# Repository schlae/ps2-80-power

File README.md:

# IBM PS/2 Model 80 Power Supply Schematics

There are multiple types of power supplies for these machines. This one is for the one marked 72X6665 / PEC 3978. This is the red switch 225W model.

## Notes

The design is an LLC resonant converter. It has a rather interesting auxiliary bias supply to power the PWM controller, so technically it is two supplies in one box.

* Inrush current into the main reservoir capacitors is limited by R117/118 and RT1/RT2. The capacitors are tied in series (to handle the 220V input case) with balancing resistors.
* The bias supply uses a preregulator that detects ~180V Vp-p and, partway through every AC cycle, cuts off a triac connected in series with a plain-old linear transformer isolated power supply. This ensures that the VCC bias supply has roughly the same voltage regardless of whether it is connected to 120V or 220V.
* The PWM controller is a SG3524 with external transistors that drive an isolation transformer in order to control the BJTs in the main power stage on the non-isolated side. The output voltage trim is set by R77, which samples both the +5V and +12V rail.
* An overcurrent comparator monitors the ripple current through the main power transformer and latches off the PWM controller if it exceeds a threshold. It also monitors the current *difference* between the two Schottky diodes in the 12V secondary side, presumably to detect Schottky diode failures.
* Every voltage (+12, -12V, +5V) is monitored for overvoltage and undervoltage. Overvoltages cause the supply to latch off. Undervoltage just deasserts the power good. Trimmer potentiometer R50 adjusts the voltage reference used by the comparators.
* The power LED is driven by the power good signal.
* The HDD LED is driven by a signal from the planar (motherboard).

## License
This work is licensed under Creative Commons Attribution-ShareAlike 4.0 International.
(C) 2024 Tube Time.

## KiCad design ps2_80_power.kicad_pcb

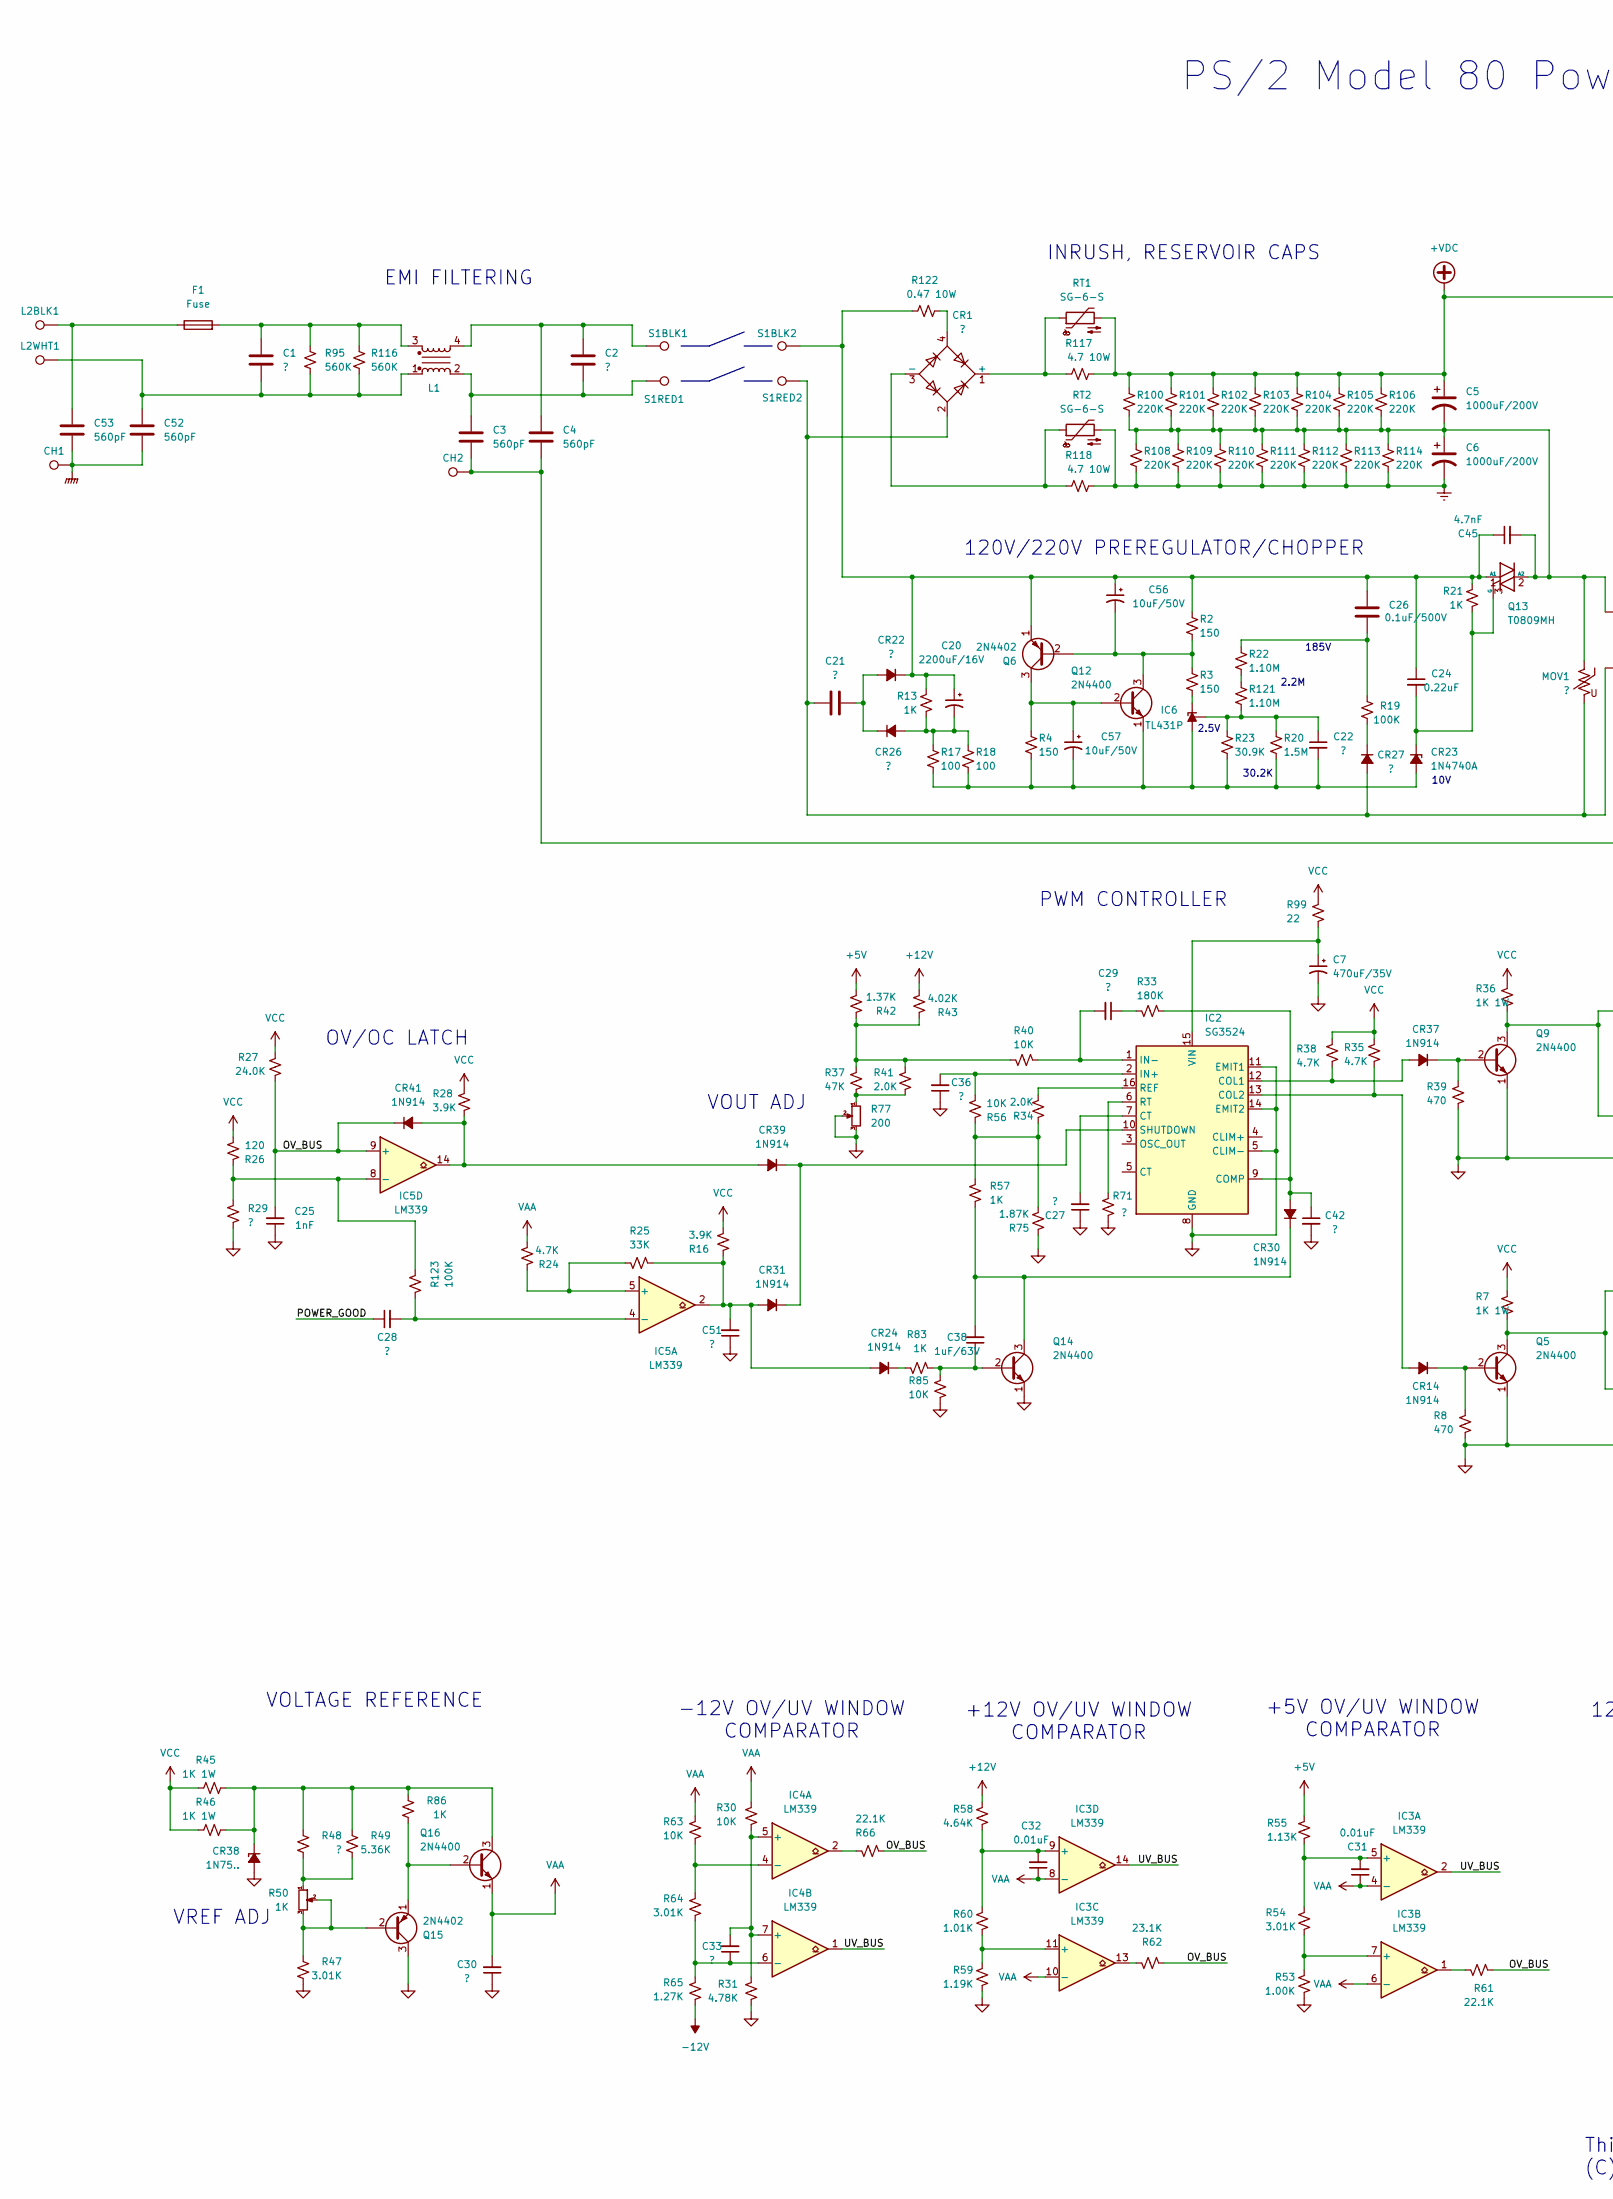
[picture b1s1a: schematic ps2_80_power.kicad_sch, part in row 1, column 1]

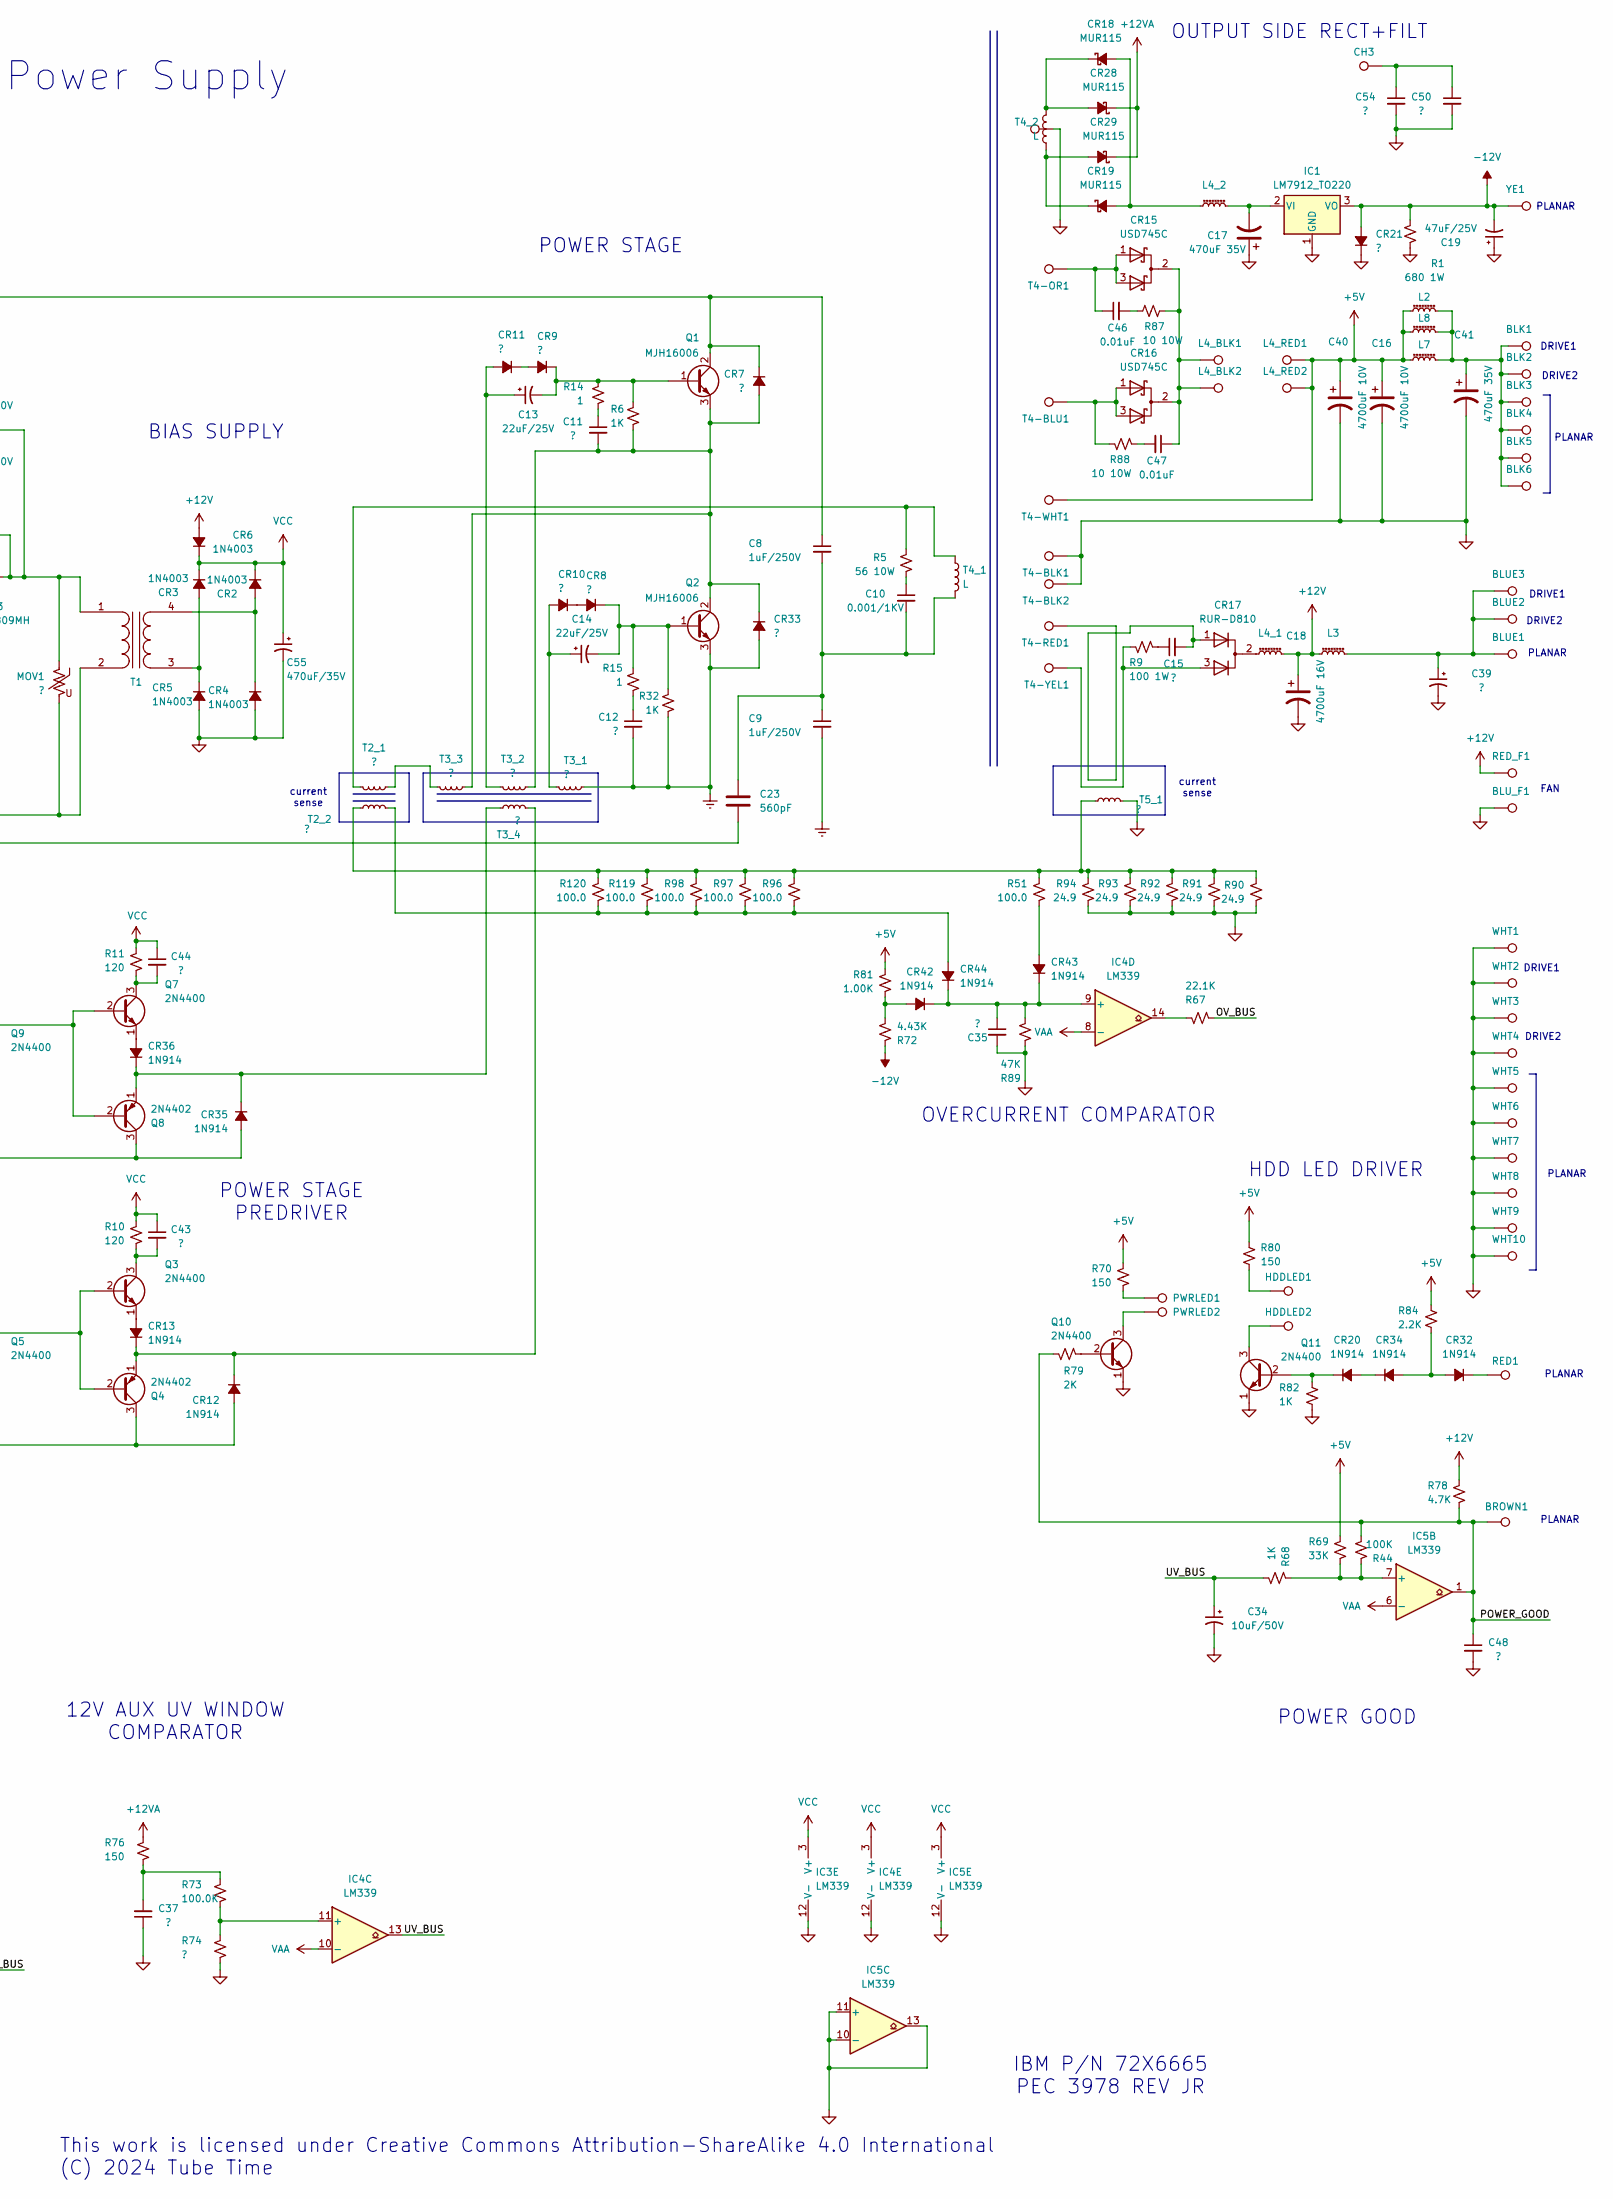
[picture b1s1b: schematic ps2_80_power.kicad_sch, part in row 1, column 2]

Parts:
BLK1, BLK2, BLK3, BLK4, BLK5, BLK6: TestPoint; SolderWire-1sqmm_1x01_D1.4mm_OD2.7mm
BLUE1, BLUE2, BLUE3: TestPoint; SolderWire-1sqmm_1x01_D1.4mm_OD2.7mm
BLU_F1: TestPoint; SolderWire-1sqmm_1x01_D1.4mm_OD2.7mm
BROWN1: TestPoint; SolderWire-1sqmm_1x01_D1.4mm_OD2.7mm
C1, C2, C21: ?; C_Rect_L29.0mm_W12.2mm_P27.50mm_MKT
C3, C4, C23, C52, C53: 560pF; C_Disc_D12.5mm_W5.0mm_P10.00mm
C5, C6: 1000uF/200V; CP_Radial_D35.0mm_P10.00mm_SnapIn
C7, C55: 470uF/35V; CP_Radial_D13.0mm_P5.00mm
C8, C9: 1uF/250V; C_Rect_L29.0mm_W7.6mm_P27.50mm_MKT
C10: 0.001/1KV; C_Disc_D7.5mm_W5.0mm_P7.50mm
C11, C12, C22, C27, C28, C36: ?; C_Axial_L3.8mm_D2.6mm_P12.50mm_Horizontal
C13, C14: 22uF/25V; CP_Radial_D5.0mm_P2.50mm
C15, C48: ?; C_Disc_D10.5mm_W5.0mm_P7.50mm
C16, C40: 4700uF 10V; CP_Radial_D16.0mm_P7.50mm
C17, C41: 470uF 35V; CP_Radial_D13.0mm_P7.50mm
C18: 4700uF 16V; CP_Radial_D16.0mm_P7.50mm
C19: 47uF/25V; CP_Radial_D5.0mm_P2.50mm
C20: 2200uF/16V; CP_Radial_D16.0mm_P7.50mm
C24: 0.22uF; C_Axial_L3.8mm_D2.6mm_P12.50mm_Horizontal
C25: 1nF; C_Axial_L3.8mm_D2.6mm_P10.00mm_Horizontal
C26: 0.1uF/500V; C_Rect_L11.0mm_W2.8mm_P10.00mm_MKT
C29, C30, C33, C35, C37, C42, C43, C44, C51: ?; C_Axial_L3.8mm_D2.6mm_P10.00mm_Horizontal
C31, C32: 0.01uF; C_Axial_L3.8mm_D2.6mm_P7.50mm_Horizontal
C34, C56, C57: 10uF/50V; CP_Radial_D5.0mm_P2.50mm
C38: 1uF/63V; C_Rect_L7.0mm_W6.0mm_P5.00mm
C39: ?; CP_Radial_D5.0mm_P2.50mm
C45: 4.7nF; C_Axial_L3.8mm_D2.6mm_P10.00mm_Horizontal
C46, C47: 0.01uF; C_Disc_D10.5mm_W5.0mm_P7.50mm
C50: ?; C_Rect_L11.0mm_W2.8mm_P10.00mm_MKT
C54: ?; C_Disc_D7.5mm_W5.0mm_P7.50mm
CH1, CH2, CH3: TestPoint; SolderWire-2.5sqmm_1x01_D2.4mm_OD3.6mm
CR1: ?; Diode_Bridge_Vishay_KBPC1
CR2, CR3, CR4, CR5, CR6: 1N4003; D_DO-41_SOD81_P12.70mm_Horizontal
CR7, CR8, CR9, CR10, CR11, CR22, CR26, CR27, CR33: ?; D_DO-41_SOD81_P12.70mm_Horizontal
CR12, CR13, CR14, CR20, CR24, CR30, CR31, CR32, CR34, CR35, CR36, CR37, CR39, CR41, CR42, CR43, CR44: 1N914; D_DO-41_SOD81_P12.70mm_Horizontal
CR15, CR16: USD745C; TO-220-3_Vertical
CR17: RUR-D810; TO-220-3_Vertical
CR18, CR19, CR28, CR29: MUR115; D_DO-41_SOD81_P10.16mm_Horizontal
CR21: ?; D_DO-201_P15.24mm_Horizontal
CR23: 1N4740A; D_DO-41_SOD81_P12.70mm_Horizontal
CR38: 1N75..; D_DO-41_SOD81_P10.16mm_Horizontal
F1: Fuse; Fuseholder_Clip-6.3x32mm_Littelfuse_102_122_Inline_P34.21x7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
HDDLED1, HDDLED2: TestPoint; SolderWire-0.1sqmm_1x01_D0.4mm_OD1mm
IC1: LM7912_TO220; TO-220-3_Vertical
IC2: SG3524; DIP254P762X635-16
IC3, IC4, IC5: LM339; DIP254P762X635-14
IC6: TL431P; DIP-8_W7.62mm
L1: Choke_Schaffner_RN102-0.3-02-22M; Choke_Schaffner_RN102-04-14.0x14.0mm
L2, L3, L7, L8: L_Ferrite_Small; L_Axial_L11.0mm_D4.5mm_P7.62mm_Vertical_Fastron_MECC
L2BLK1, L2WHT1, L4_BLK1, L4_BLK2, L4_RED1, L4_RED2: TestPoint; SolderWire-2.5sqmm_1x01_D2.4mm_OD3.6mm
L4_1, L4_2: L_Ferrite_Small; L_Axial_L29.9mm_D14.0mm_P38.00mm_Horizontal_Vishay_IHA-105
MOV1: ?; RV_Disc_D21.5mm_W4.3mm_P10mm
PWRLED1, PWRLED2: TestPoint; SolderWire-0.1sqmm_1x01_D0.4mm_OD1mm
Q1, Q2: MJH16006; TO-247-3_Vertical
Q3, Q5, Q7, Q9, Q10, Q14, Q16: 2N4400; TO-92_Inline
Q4, Q8, Q15: 2N4402; TO-92_Inline
Q6: 2N4402; TO-92_Inline_Wide
Q11, Q12: 2N4400; TO-92_Inline_Wide
Q13: T0809MH; TO-220-3_Vertical
R1: 680 1W; R_Axial_DIN0207_L6.3mm_D2.5mm_P15.24mm_Horizontal
R2, R3, R4, R70, R76, R80: 150; R_Axial_DIN0309_L9.0mm_D3.2mm_P12.70mm_Horizontal
R5: 56 10W; R_Axial_DIN0309_L9.0mm_D3.2mm_P15.24mm_Horizontal
R6, R13, R21, R32, R57, R68, R82, R83, R86: 1K; R_Axial_DIN0309_L9.0mm_D3.2mm_P12.70mm_Horizontal
R7, R36, R45, R46: 1K 1W; R_Axial_DIN0207_L6.3mm_D2.5mm_P15.24mm_Horizontal
R8, R39: 470; R_Axial_DIN0309_L9.0mm_D3.2mm_P12.70mm_Horizontal
R9: 100 1W; R_Axial_DIN0207_L6.3mm_D2.5mm_P15.24mm_Horizontal
R10, R11: 120; R_Axial_DIN0207_L6.3mm_D2.5mm_P15.24mm_Horizontal
R14, R15: 1; R_Axial_DIN0309_L9.0mm_D3.2mm_P12.70mm_Horizontal
R16, R28: 3.9K; R_Axial_DIN0309_L9.0mm_D3.2mm_P12.70mm_Horizontal
R17, R18: 100; R_Axial_DIN0309_L9.0mm_D3.2mm_P15.24mm_Horizontal
R19, R44, R123: 100K; R_Axial_DIN0309_L9.0mm_D3.2mm_P12.70mm_Horizontal
R20: 1.5M; R_Axial_DIN0309_L9.0mm_D3.2mm_P12.70mm_Horizontal
R22, R121: 1.10M; R_Axial_DIN0309_L9.0mm_D3.2mm_P12.70mm_Horizontal
R23: 30.9K; R_Axial_DIN0309_L9.0mm_D3.2mm_P12.70mm_Horizontal
R24, R35, R38, R78: 4.7K; R_Axial_DIN0309_L9.0mm_D3.2mm_P12.70mm_Horizontal
R25, R69: 33K; R_Axial_DIN0309_L9.0mm_D3.2mm_P12.70mm_Horizontal
R26: 120; R_Axial_DIN0309_L9.0mm_D3.2mm_P12.70mm_Horizontal
R27: 24.0K; R_Axial_DIN0309_L9.0mm_D3.2mm_P12.70mm_Horizontal
R29, R48, R71, R74: ?; R_Axial_DIN0309_L9.0mm_D3.2mm_P12.70mm_Horizontal
R30, R40, R56, R63, R85: 10K; R_Axial_DIN0309_L9.0mm_D3.2mm_P12.70mm_Horizontal
R31: 4.78K; R_Axial_DIN0309_L9.0mm_D3.2mm_P12.70mm_Horizontal
R33: 180K; R_Axial_DIN0309_L9.0mm_D3.2mm_P12.70mm_Horizontal
R34, R41: 2.0K; R_Axial_DIN0309_L9.0mm_D3.2mm_P12.70mm_Horizontal
R37, R89: 47K; R_Axial_DIN0309_L9.0mm_D3.2mm_P12.70mm_Horizontal
R42: 1.37K; R_Axial_DIN0309_L9.0mm_D3.2mm_P12.70mm_Horizontal
R43: 4.02K; R_Axial_DIN0309_L9.0mm_D3.2mm_P12.70mm_Horizontal
R47, R54, R64: 3.01K; R_Axial_DIN0309_L9.0mm_D3.2mm_P12.70mm_Horizontal
R49: 5.36K; R_Axial_DIN0309_L9.0mm_D3.2mm_P12.70mm_Horizontal
R50: 1K; Potentiometer_Bourns_3386C_Horizontal
R51, R96, R97, R98, R119, R120: 100.0; R_Axial_DIN0309_L9.0mm_D3.2mm_P12.70mm_Horizontal
R53, R81: 1.00K; R_Axial_DIN0309_L9.0mm_D3.2mm_P12.70mm_Horizontal
R55: 1.13K; R_Axial_DIN0309_L9.0mm_D3.2mm_P12.70mm_Horizontal
R58: 4.64K; R_Axial_DIN0309_L9.0mm_D3.2mm_P12.70mm_Horizontal
R59: 1.19K; R_Axial_DIN0309_L9.0mm_D3.2mm_P12.70mm_Horizontal
R60: 1.01K; R_Axial_DIN0309_L9.0mm_D3.2mm_P12.70mm_Horizontal
R61, R66, R67: 22.1K; R_Axial_DIN0309_L9.0mm_D3.2mm_P12.70mm_Horizontal
R62: 23.1K; R_Axial_DIN0309_L9.0mm_D3.2mm_P12.70mm_Horizontal
R65: 1.27K; R_Axial_DIN0309_L9.0mm_D3.2mm_P12.70mm_Horizontal
R72: 4.43K; R_Axial_DIN0309_L9.0mm_D3.2mm_P12.70mm_Horizontal
R73: 100.0K; R_Axial_DIN0309_L9.0mm_D3.2mm_P12.70mm_Horizontal
R75: 1.87K; R_Axial_DIN0309_L9.0mm_D3.2mm_P12.70mm_Horizontal
R77: 200; Potentiometer_Bourns_3386C_Horizontal
R79: 2K; R_Axial_DIN0309_L9.0mm_D3.2mm_P12.70mm_Horizontal
R84: 2.2K; R_Axial_DIN0309_L9.0mm_D3.2mm_P12.70mm_Horizontal
R87, R88: 10 10W; R_Axial_DIN0309_L9.0mm_D3.2mm_P15.24mm_Horizontal
R90, R91, R92, R93, R94: 24.9; R_Axial_DIN0309_L9.0mm_D3.2mm_P12.70mm_Horizontal
R95, R116: 560K; R_Axial_DIN0309_L9.0mm_D3.2mm_P15.24mm_Horizontal
R99: 22; R_Axial_DIN0309_L9.0mm_D3.2mm_P12.70mm_Horizontal
R100, R101, R102, R103, R104, R105, R106, R108, R109, R110, R111, R112, R113, R114: 220K; R_Axial_DIN0309_L9.0mm_D3.2mm_P15.24mm_Horizontal
R117, R118: 4.7 10W; R_Axial_DIN0309_L9.0mm_D3.2mm_P15.24mm_Horizontal
R122: 0.47 10W; R_Axial_DIN0309_L9.0mm_D3.2mm_P15.24mm_Horizontal
RED1: TestPoint; SolderWire-1sqmm_1x01_D1.4mm_OD2.7mm
RED_F1: TestPoint; SolderWire-1sqmm_1x01_D1.4mm_OD2.7mm
RT1, RT2: SG-6-S
S1BLK1, S1BLK2, S1RED1, S1RED2: TestPoint; SolderWire-2.5sqmm_1x01_D2.4mm_OD3.6mm
T1: Transformer_1P_1S; Transformer_Toroid_Horizontal_D14.0mm_Amidon-T50
T2_1, T3_3: ?; C_Rect_L16.5mm_W4.7mm_P15.00mm_MKT
T2_2, T5_1: ?; C_Rect_L9.0mm_W2.5mm_P7.50mm_MKT
T3_1, T3_2, T3_4: ?; C_Rect_L7.0mm_W3.5mm_P5.00mm
T4-BLK1, T4-BLK2, T4-BLU1, T4-OR1, T4-RED1, T4-WHT1, T4-YEL1: TestPoint; SolderWire-2.5sqmm_1x01_D2.4mm_OD3.6mm
T4_1: L; C_Rect_L24.0mm_W7.0mm_P22.50mm_MKT
T4_2: L; C_Rect_L19.0mm_W9.0mm_P15.00mm_MKS4
T4_2A1: TestPoint; SolderWire-0.75sqmm_1x01_D1.25mm_OD2.3mm
WHT1, WHT2, WHT3, WHT4, WHT5, WHT6, WHT7, WHT8, WHT9, WHT10: TestPoint; SolderWire-1sqmm_1x01_D1.4mm_OD2.7mm
YE1: TestPoint; SolderWire-1sqmm_1x01_D1.4mm_OD2.7mm

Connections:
+5V: C16.1, C40.1, L2.1, L4_RED1.1, L4_RED2.1, L7.1, L8.1, R42.1, R55.2, R69.2, R70.2, R80.2, R81.1, R84.1, T4-WHT1.1
+12V: C18.1, CR6.2 (A), L3.1, L4_1.2, R43.1, R58.1, R78.2, RED_F1.1
+12VA: CR28.1 (K), CR29.1 (K), R76.2
+VDC: C5.1, C8.1, CR7.1 (K), Q1.2 (C), R100.1, R101.1, R102.1, R103.1, R104.1, R105.1, R106.1, R117.2, RT1.2
-12V: C19.2, CR21.2 (A), IC1.3 (VO), R1.1, R65.2, R72.1, YE1.1
/OV_BUS: C25.2, CR41.1 (K), IC5.9 (+), R27.1, R61.2, R62.2, R66.1, R67.1
/POWER_GOOD: BROWN1.1, C28.1, C48.1, IC5.1, R44.1, R78.1, R79.2
/UV_BUS: C34.1, IC3.2, IC3.14, IC4.1, IC4.13, R68.1
Earth: C6.2, C9.2, C12.2, CR33.2 (A), Q2.3 (E), R32.2, R108.2, R109.2, R110.2, R111.2, R112.2, R113.2, R114.2, R118.2, RT2.2, T3_1.1
GND: BLU_F1.1, C7.2, C16.2, C17.1, C18.2, C19.1, C25.1, C27.1, C30.1, C34.2, C35.2, C36.1, C37.1, C39.2, C40.2, C41.2, C42.2, C48.2, C50.2, C51.1, C54.2, C55.2, CR4.2 (A), CR5.2 (A), CR12.2 (A), CR21.1 (K), CR35.2 (A), CR38.2 (A), IC1.1 (GND), IC2.5 (CLIM-), IC2.8 (GND), IC2.11 (EMIT1), IC2.14 (EMIT2), IC3.12 (V-), IC4.12 (V-), IC5.10 (-), IC5.11 (+), IC5.12 (V-), IC5.13, Q4.3 (C), Q5.1 (E), Q8.3 (C), Q9.1 (E), Q10.1 (E), Q11.1 (E), Q14.1 (E), Q15.3 (C), R1.2, R8.1, R29.1, R31.2, R39.1, R47.1, R53.2, R59.2, R71.2, R74.1, R75.2, R77.2, R77.3, R82.2, R85.1, R89.1, R90.2, R91.2, R92.2, R93.2, R94.2, T4-BLK1.1, T4-BLK2.1, T4_2A1.1, T5_1.1, WHT1.1, WHT2.1, WHT3.1, WHT4.1, WHT5.1, WHT6.1, WHT7.1, WHT8.1, WHT9.1, WHT10.1
GNDPWR: C52.2, C53.2, CH1.1
unnamed: BLK1.1, BLK2.1, BLK3.1, BLK4.1, BLK5.1, BLK6.1, C41.1, L2.2, L7.2, L8.2
unnamed: BLUE1.1, BLUE2.1, BLUE3.1, C39.1, L3.2
unnamed: C1.1, F1.2, L1.3, R95.1, R116.1
unnamed: C1.2, C52.1, L1.1, L2WHT1.1, R95.2, R116.2
unnamed: C2.1, C4.1, L1.4, S1BLK1.1
unnamed: C2.2, C3.1, L1.2, S1RED1.1
unnamed: C10.1, R5.1
unnamed: C8.2, C9.1, C10.2, C23.2, T4_1.2
unnamed: C11.1, R14.2
unnamed: C12.1, R15.2
unnamed: C15.1, R9.1
unnamed: C15.2, CR17.1 (K), T4-RED1.1
unnamed: C3.2, C4.2, C23.1, CH2.1
unnamed: C26.2, R19.2, R22.1
unnamed: C27.2, IC2.7 (CT)
unnamed: C29.1, R33.2
unnamed: C37.2, R73.2, R76.1
unnamed: C46.1, CR15.1 (K), CR15.3 (K), T4-OR1.1
unnamed: C46.2, R87.1
unnamed: C47.2, R88.1
unnamed: C50.1, C54.1, CH3.1
unnamed: C53.1, F1.1, L2BLK1.1
unnamed: CR1.1 (+), R117.1, RT1.1
unnamed: CR1.3 (-), R118.1, RT2.1
unnamed: CR1.4, R122.2
unnamed: CR2.2 (A), CR4.1 (K), T1.4 (SB)
unnamed: CR3.2 (A), CR5.1 (K), T1.3 (SA)
unnamed: C14.2, CR8.1 (K), Q2.1 (B), R15.1, R32.1
unnamed: C13.2, CR9.1 (K), Q1.1 (B), R6.1, R14.1
unnamed: C14.1, CR10.2 (A), T3_1.2
unnamed: CR8.2 (A), CR10.1 (K)
unnamed: C13.1, CR11.2 (A), T3_2.2
unnamed: CR9.2 (A), CR11.1 (K)
unnamed: CR12.1 (K), CR13.1 (K), Q4.1 (E), T3_4.2
unnamed: CR13.2 (A), Q3.1 (E)
unnamed: CR14.2 (A), IC2.13 (COL2), R35.1
unnamed: CR14.1 (K), Q5.2 (B), R8.2
unnamed: C47.1, CR15.2 (A), CR16.2 (A), L4_BLK1.1, L4_BLK2.1, R87.2
unnamed: CR16.1 (K), CR16.3 (K), R88.2, T4-BLU1.1
unnamed: CR17.2 (A), L4_1.1
unnamed: CR17.3 (K), R9.2, T4-YEL1.1
unnamed: CR18.2 (A), CR19.2 (A), L4_2.1
unnamed: CR18.1 (K), CR28.2 (A), T4_2.1
unnamed: CR19.1 (K), CR29.2 (A), T4_2.2
unnamed: CR20.2 (A), CR34.1 (K)
unnamed: CR20.1 (K), Q11.2 (B), R82.1
unnamed: C21.2, CR22.2 (A), CR26.1 (K)
unnamed: C20.1, C24.1, C26.1, C45.1, C56.1, CR22.1 (K), Q6.1 (E), Q13.1 (A1), R2.1, R13.1, R21.1, R122.1, S1BLK2.1
unnamed: C22.2, C57.2, CR23.2 (A), IC6.6 (A), Q12.1 (E), R4.2, R17.2, R18.2, R20.2, R23.2
unnamed: C24.2, CR23.1 (K), Q13.3 (G), R21.2
unnamed: C51.2, CR24.2 (A), CR31.2 (A), IC5.2, R16.1, R25.2
unnamed: CR24.1 (K), R83.1
unnamed: C20.2, CR26.2 (A), R13.2, R17.1, R18.1
unnamed: C21.1, CR1.2, CR27.2 (A), MOV1.2, S1RED2.1, T1.2 (AB)
unnamed: CR27.1 (K), R19.1
unnamed: C42.1, CR30.2 (A), IC2.9 (COMP), R33.1
unnamed: C38.2, CR30.1 (K), Q14.3 (C), R57.1
unnamed: CR31.1 (K), CR39.1 (K), IC2.10 (SHUTDOWN)
unnamed: CR32.2 (A), CR34.2 (A), R84.2
unnamed: CR32.1 (K), RED1.1
unnamed: C11.2, CR7.2 (A), CR33.1 (K), Q1.3 (E), Q2.2 (C), R6.2, T3_2.1, T3_3.1
unnamed: CR35.1 (K), CR36.1 (K), Q8.1 (E), T3_4.1
unnamed: CR36.2 (A), Q7.1 (E)
unnamed: CR37.2 (A), IC2.12 (COL1), R38.1
unnamed: CR37.1 (K), Q9.2 (B), R39.2
unnamed: CR38.1 (K), Q16.3 (C), R45.2, R46.2, R48.2, R49.2, R86.2
unnamed: CR39.2 (A), CR41.2 (A), IC5.14, R28.1
unnamed: CR42.2 (A), R72.2, R81.2
unnamed: C35.1, CR42.1 (K), CR43.1 (K), CR44.1 (K), IC4.9 (+), R89.2
unnamed: CR43.2 (A), R51.2
unnamed: CR44.2 (A), R96.2, R97.2, R98.2, R119.2, R120.2, T2_2.1
unnamed: HDDLED1.1, R80.1
unnamed: C17.2, IC1.2 (VI), L4_2.2
unnamed: C36.2, IC2.2 (IN+), R56.1
unnamed: C29.2, IC2.1 (IN-), R40.1
unnamed: IC2.16 (REF), R34.1
unnamed: IC2.6 (RT), R71.1
unnamed: C7.1, IC2.15 (VIN), R99.1
unnamed: IC3.1, R61.1
unnamed: IC3.13, R62.1
unnamed: C31.2, IC3.5 (+), R54.2, R55.1
unnamed: IC3.7 (+), R53.1, R54.1
unnamed: IC3.11 (+), R59.1, R60.2
unnamed: C32.2, IC3.9 (+), R58.2, R60.1
unnamed: IC4.2, R66.2
unnamed: IC4.14, R67.2
unnamed: C33.2, IC4.5 (+), IC4.7 (+), R30.2, R31.1
unnamed: IC4.4 (-), R63.2, R64.1
unnamed: C33.1, IC4.6 (-), R64.2, R65.1
unnamed: IC4.11 (+), R73.1, R74.2
unnamed: IC5.5 (+), R24.2, R25.1
unnamed: C28.2, IC5.4 (-), R123.1
unnamed: IC5.7 (+), R44.2, R68.2, R69.1
unnamed: IC5.8 (-), R26.2, R29.2, R123.2
unnamed: IC6.1 (K), R3.2
unnamed: C22.1, IC6.8 (REF), R20.1, R23.1, R121.2
unnamed: PWRLED1.1, R70.1
unnamed: Q3.2 (B), Q4.2 (B), Q5.3 (C), R7.1
unnamed: C43.2, Q3.3 (C), R10.1
unnamed: Q7.2 (B), Q8.2 (B), Q9.3 (C), R36.1
unnamed: C44.2, Q7.3 (C), R11.1
unnamed: Q10.2 (B), R79.1
unnamed: PWRLED2.1, Q10.3 (C)
unnamed: HDDLED2.1, Q11.3 (C)
unnamed: C57.1, Q6.3 (C), Q12.2 (B), R4.1
unnamed: C56.2, Q6.2 (B), Q12.3 (C), R2.2, R3.1
unnamed: C5.2, C6.1, C45.2, MOV1.1, Q13.2 (A2), R100.2, R101.2, R102.2, R103.2, R104.2, R105.2, R106.2, R108.1, R109.1, R110.1, R111.1, R112.1, R113.1, R114.1, T1.1 (AA)
unnamed: C38.1, Q14.2 (B), R83.2, R85.2
unnamed: Q15.2 (B), R47.2, R50.2, R50.3
unnamed: Q15.1 (E), Q16.2 (B), R86.1
unnamed: R5.2, T2_1.1, T4_1.1
unnamed: R34.2, R56.2, R57.2, R75.1
unnamed: R37.1, R41.1, R77.1
unnamed: R37.2, R40.2, R41.2, R42.2, R43.2
unnamed: R48.1, R49.1, R50.1
unnamed: R51.1, R90.1, R91.1, R92.1, R93.1, R94.1, R96.1, R97.1, R98.1, R119.1, R120.1, T2_2.2, T5_1.2
unnamed: R22.2, R121.1
unnamed: T2_1.2, T3_3.2
VAA: C30.2, C31.1, C32.1, IC3.4 (-), IC3.6 (-), IC3.8 (-), IC3.10 (-), IC4.8 (-), IC4.10 (-), IC5.6 (-), Q16.1 (E), R24.1, R30.1, R63.1
VCC: C43.1, C44.1, C55.1, CR2.1 (K), CR3.1 (K), CR6.1 (K), IC3.3 (V+), IC4.3 (V+), IC5.3 (V+), R7.2, R10.2, R11.2, R16.2, R26.1, R27.2, R28.2, R35.2, R36.2, R38.2, R45.1, R46.1, R99.2

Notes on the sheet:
PLANAR
DRIVE1
POWER GOOD
+5V OV/UV WINDOW COMPARATOR
10V
2.2M
12V AUX UV WINDOW COMPARATOR
OVERCURRENT COMPARATOR
2.5V
DRIVE2
OUTPUT SIDE RECT+FILT
current sense
FAN
POWER STAGE PREDRIVER
+12V OV/UV WINDOW COMPARATOR
HDD LED DRIVER
-12V OV/UV WINDOW COMPARATOR
120V/220V PREREGULATOR/CHOPPER
OV/OC LATCH
This work is licensed under Creative Commons Attribution-ShareAlike 4.0 International (C) 2024 Tube Time
VOUT ADJ
VREF ADJ
INRUSH, RESERVOIR CAPS
PS/2 Model 80 Power Supply
VOLTAGE REFERENCE
185V
EMI FILTERING
PWM CONTROLLER
30.2K
POWER STAGE
BIAS SUPPLY
IBM P/N 72X6665 PEC 3978 REV JR

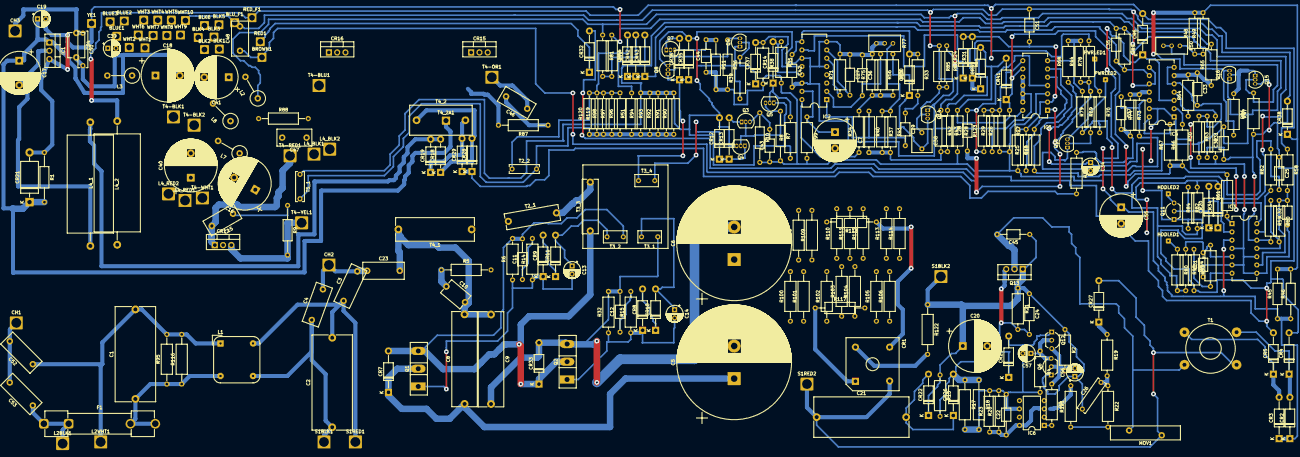
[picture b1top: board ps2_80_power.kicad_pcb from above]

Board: 2 copper layers, 307 parts (0 on the bottom side), 131 nets.

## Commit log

2024-10-08 added readme
2024-10-09 a few part value updates
